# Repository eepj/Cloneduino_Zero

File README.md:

# Cloneduino_Zero
An Arduino Zero clone in a breadboard-compatible form factor.

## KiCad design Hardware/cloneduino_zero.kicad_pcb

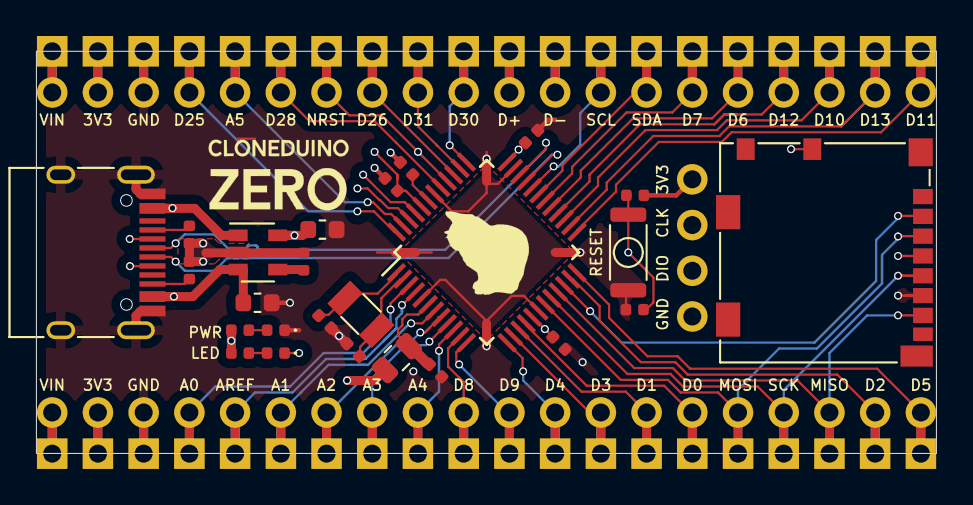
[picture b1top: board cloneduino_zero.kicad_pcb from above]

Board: 4 copper layers, 50.0 x 22.3 mm, 30 parts (0 on the bottom side), 49 nets.

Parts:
C1, C2, C3, C4, C5, C7, C9: 100n; C_0402_1005Metric
C6, C8: 4.7u; C_0603_1608Metric
C10, C11: 15p; C_0402_1005Metric
D1: D13; LED_0402_1005Metric
D2: PWR; LED_0402_1005Metric
J1: USB-C Receptacle; USB_C_Receptacle_HRO_TYPE-C-31-M-12
J2: MicroSD Slot; microSD_HC_Molex_104031-0811
J3, J4, J6, J7: Conn_01x20; PinHeader_1x20_P2.54mm_Vertical
J5: SWD; PinHeader_1x04_P2.54mm_Vertical
L1: L; L_0805_2012Metric
R1, R2, R3, R4, R5: 5k1; R_0402_1005Metric
SW1: Reset Switch; SW_Push_SPST_NO_Alps_SKRK
U1: SPX3819M5-L-3-3; SOT-23-5
U2: ATSAMD21G18A-A; TQFP-48_7x7mm_P0.5mm
Y1: 32.768kHz; Crystal_SMD_3215-2Pin_3.2x1.5mm

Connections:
+3.3VA: C4.1, L1.2, U2.6
+3V3: C1.1, C2.1, C3.1, C8.1, J2.4, J3.2, J4.19, J5.1, J6.2, J7.19, L1.1, R1.2, R2.1, R5.1, U1.5, U2.17, U2.36, U2.44
+5V: C6.1, J1.A4, J1.A9, J1.B4, J1.B9, J3.1, J4.20, J6.1, J7.20, U1.1, U1.3
/NRST: C9.1, J4.14, J7.14, R5.2, SW1.1, U2.40
/PA00: C10.1, U2.1, Y1.1
/PA01: C11.1, U2.2, Y1.2
/PA02: J3.4, J6.4, U2.3
/PA03: J3.5, J6.5, U2.4
/PA04: J3.8, J6.8, U2.9
/PA05: J3.9, J6.9, U2.10
/PA06: J3.10, J6.10, U2.11
/PA07: J3.11, J6.11, U2.12
/PA08: J3.12, J6.12, U2.13
/PA09: J3.13, J6.13, U2.14
/PA10: J3.14, J6.14, U2.15
/PA11: J3.15, J6.15, U2.16
/PA12: J2.7, J3.18, J6.18, U2.21
/PA13: J2.2, U2.22
/PA14: J3.19, J6.19, U2.23
/PA15: J3.20, J6.20, U2.24
/PA16: J4.1, J7.1, U2.25
/PA17: D1.1, J4.2, J7.2, U2.26
/PA18: J4.3, J7.3, U2.27
/PA19: J4.4, J7.4, U2.28
/PA20: J4.5, J7.5, U2.29
/PA21: J4.6, J7.6, U2.30
/PA22: J4.7, J7.7, U2.31
/PA23: J4.8, J7.8, U2.32
/PA27: J4.13, J7.13, U2.39
/PA28: J4.15, J7.15, U2.41
/PA30: J5.2, U2.45
/PA31: J5.3, U2.46
/PB02: J4.16, J7.16, U2.47
/PB03: J4.17, J7.17, U2.48
/PB08: J3.6, J6.6, U2.7
/PB09: J3.7, J6.7, U2.8
/PB10: J2.3, J3.16, J6.16, U2.19
/PB11: J2.5, J3.17, J6.17, U2.20
/PB22: J4.11, J7.11, U2.37
/PB23: J4.12, J7.12, U2.38
/USB_D+: J1.A6, J1.B6, J4.10, J7.10, U2.34
/USB_D-: J1.A7, J1.B7, J4.9, J7.9, U2.33
/VDDCORE: C5.1, U2.43
GND: C1.2, C2.2, C3.2, C4.2, C5.2, C6.2, C7.2, C8.2, C9.2, C10.2, C11.2, D2.1, J1.A1, J1.A12, J1.B1, J1.B12, J1.S1, J2.6, J2.9, J3.3, J4.18, J5.4, J6.3, J7.18, R3.1, R4.1, SW1.2, U1.2, U2.5, U2.18, U2.35, U2.42
unnamed: C7.1, U1.4
unnamed: D1.2, R1.1
unnamed: D2.2, R2.2
unnamed: J1.A5, R3.2
unnamed: J1.B5, R4.2

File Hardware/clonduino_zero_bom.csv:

Designator,Value,Footprint,Qty
C1,100n,Capacitor_SMD:C_0402_1005Metric,1
C2,100n,Capacitor_SMD:C_0402_1005Metric,1
C3,100n,Capacitor_SMD:C_0402_1005Metric,1
C4,100n,Capacitor_SMD:C_0402_1005Metric,1
C5,100n,Capacitor_SMD:C_0402_1005Metric,1
C6,4.7u,Capacitor_SMD:C_0603_1608Metric,1
C7,100n,Capacitor_SMD:C_0402_1005Metric,1
C8,4.7u,Capacitor_SMD:C_0603_1608Metric,1
C9,100n,Capacitor_SMD:C_0402_1005Metric,1
C10,15p,Capacitor_SMD:C_0402_1005Metric,1
C11,15p,Capacitor_SMD:C_0402_1005Metric,1
D1,D13,LED_SMD:LED_0402_1005Metric,1
D2,PWR,LED_SMD:LED_0402_1005Metric,1
J1,USB-C Receptacle,Connector_USB:USB_C_Receptacle_HRO_TYPE-C-31-M-12,1
J2,MicroSD Slot,Connector_Card:microSD_HC_Molex_104031-0811,1
J3,Conn_01x20,Connector_PinHeader_2.54mm:PinHeader_1x20_P2.54mm_Vertical,1
J4,Conn_01x20,Connector_PinHeader_2.54mm:PinHeader_1x20_P2.54mm_Vertical,1
J5,SWD,Connector_PinHeader_2.54mm:PinHeader_1x04_P2.54mm_Vertical,1
L1,L,Inductor_SMD:L_0805_2012Metric,1
R1,5k1,Resistor_SMD:R_0402_1005Metric,1
R2,5k1,Resistor_SMD:R_0402_1005Metric,1
R3,5k1,Resistor_SMD:R_0402_1005Metric,1
R4,5k1,Resistor_SMD:R_0402_1005Metric,1
R5,5k1,Resistor_SMD:R_0402_1005Metric,1
SW1,Reset Switch,Button_Switch_SMD:SW_Push_SPST_NO_Alps_SKRK,1
U1,SPX3819M5-L-3-3,Package_TO_SOT_SMD:SOT-23-5,1
U2,ATSAMD21G18A-A,Package_QFP:TQFP-48_7x7mm_P0.5mm,1
Y1,32.768kHz,Crystal:Crystal_SMD_3215-2Pin_3.2x1.5mm,1

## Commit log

2021-04-11 Import KiCad project
2021-04-11 Update page setup
2021-04-22 Fix SD MOSI connection
2021-04-22 Silkscreen fixes
2021-04-22 Fix schematics LED orientation
2021-06-06 Fix pin assignments
2021-06-06 Fix bottom silkscreen references
2021-06-06 Update schematics PDF
2021-06-06 Change D25 and D26 to output pins
2021-06-06 Rename reset switch
2021-06-06 Add interrupt line reference
2022-07-01 Optimize BOM
2022-07-03 Keep PCB width under 50 mm
2022-07-03 Update BOM
2022-07-26 Change silkscreen markings
2022-07-30 Add solder points
2022-07-30 Update schematics
2022-07-30 Remove alignment targets
2022-07-30 Generate new gerber files
2022-08-05 Route all traces
